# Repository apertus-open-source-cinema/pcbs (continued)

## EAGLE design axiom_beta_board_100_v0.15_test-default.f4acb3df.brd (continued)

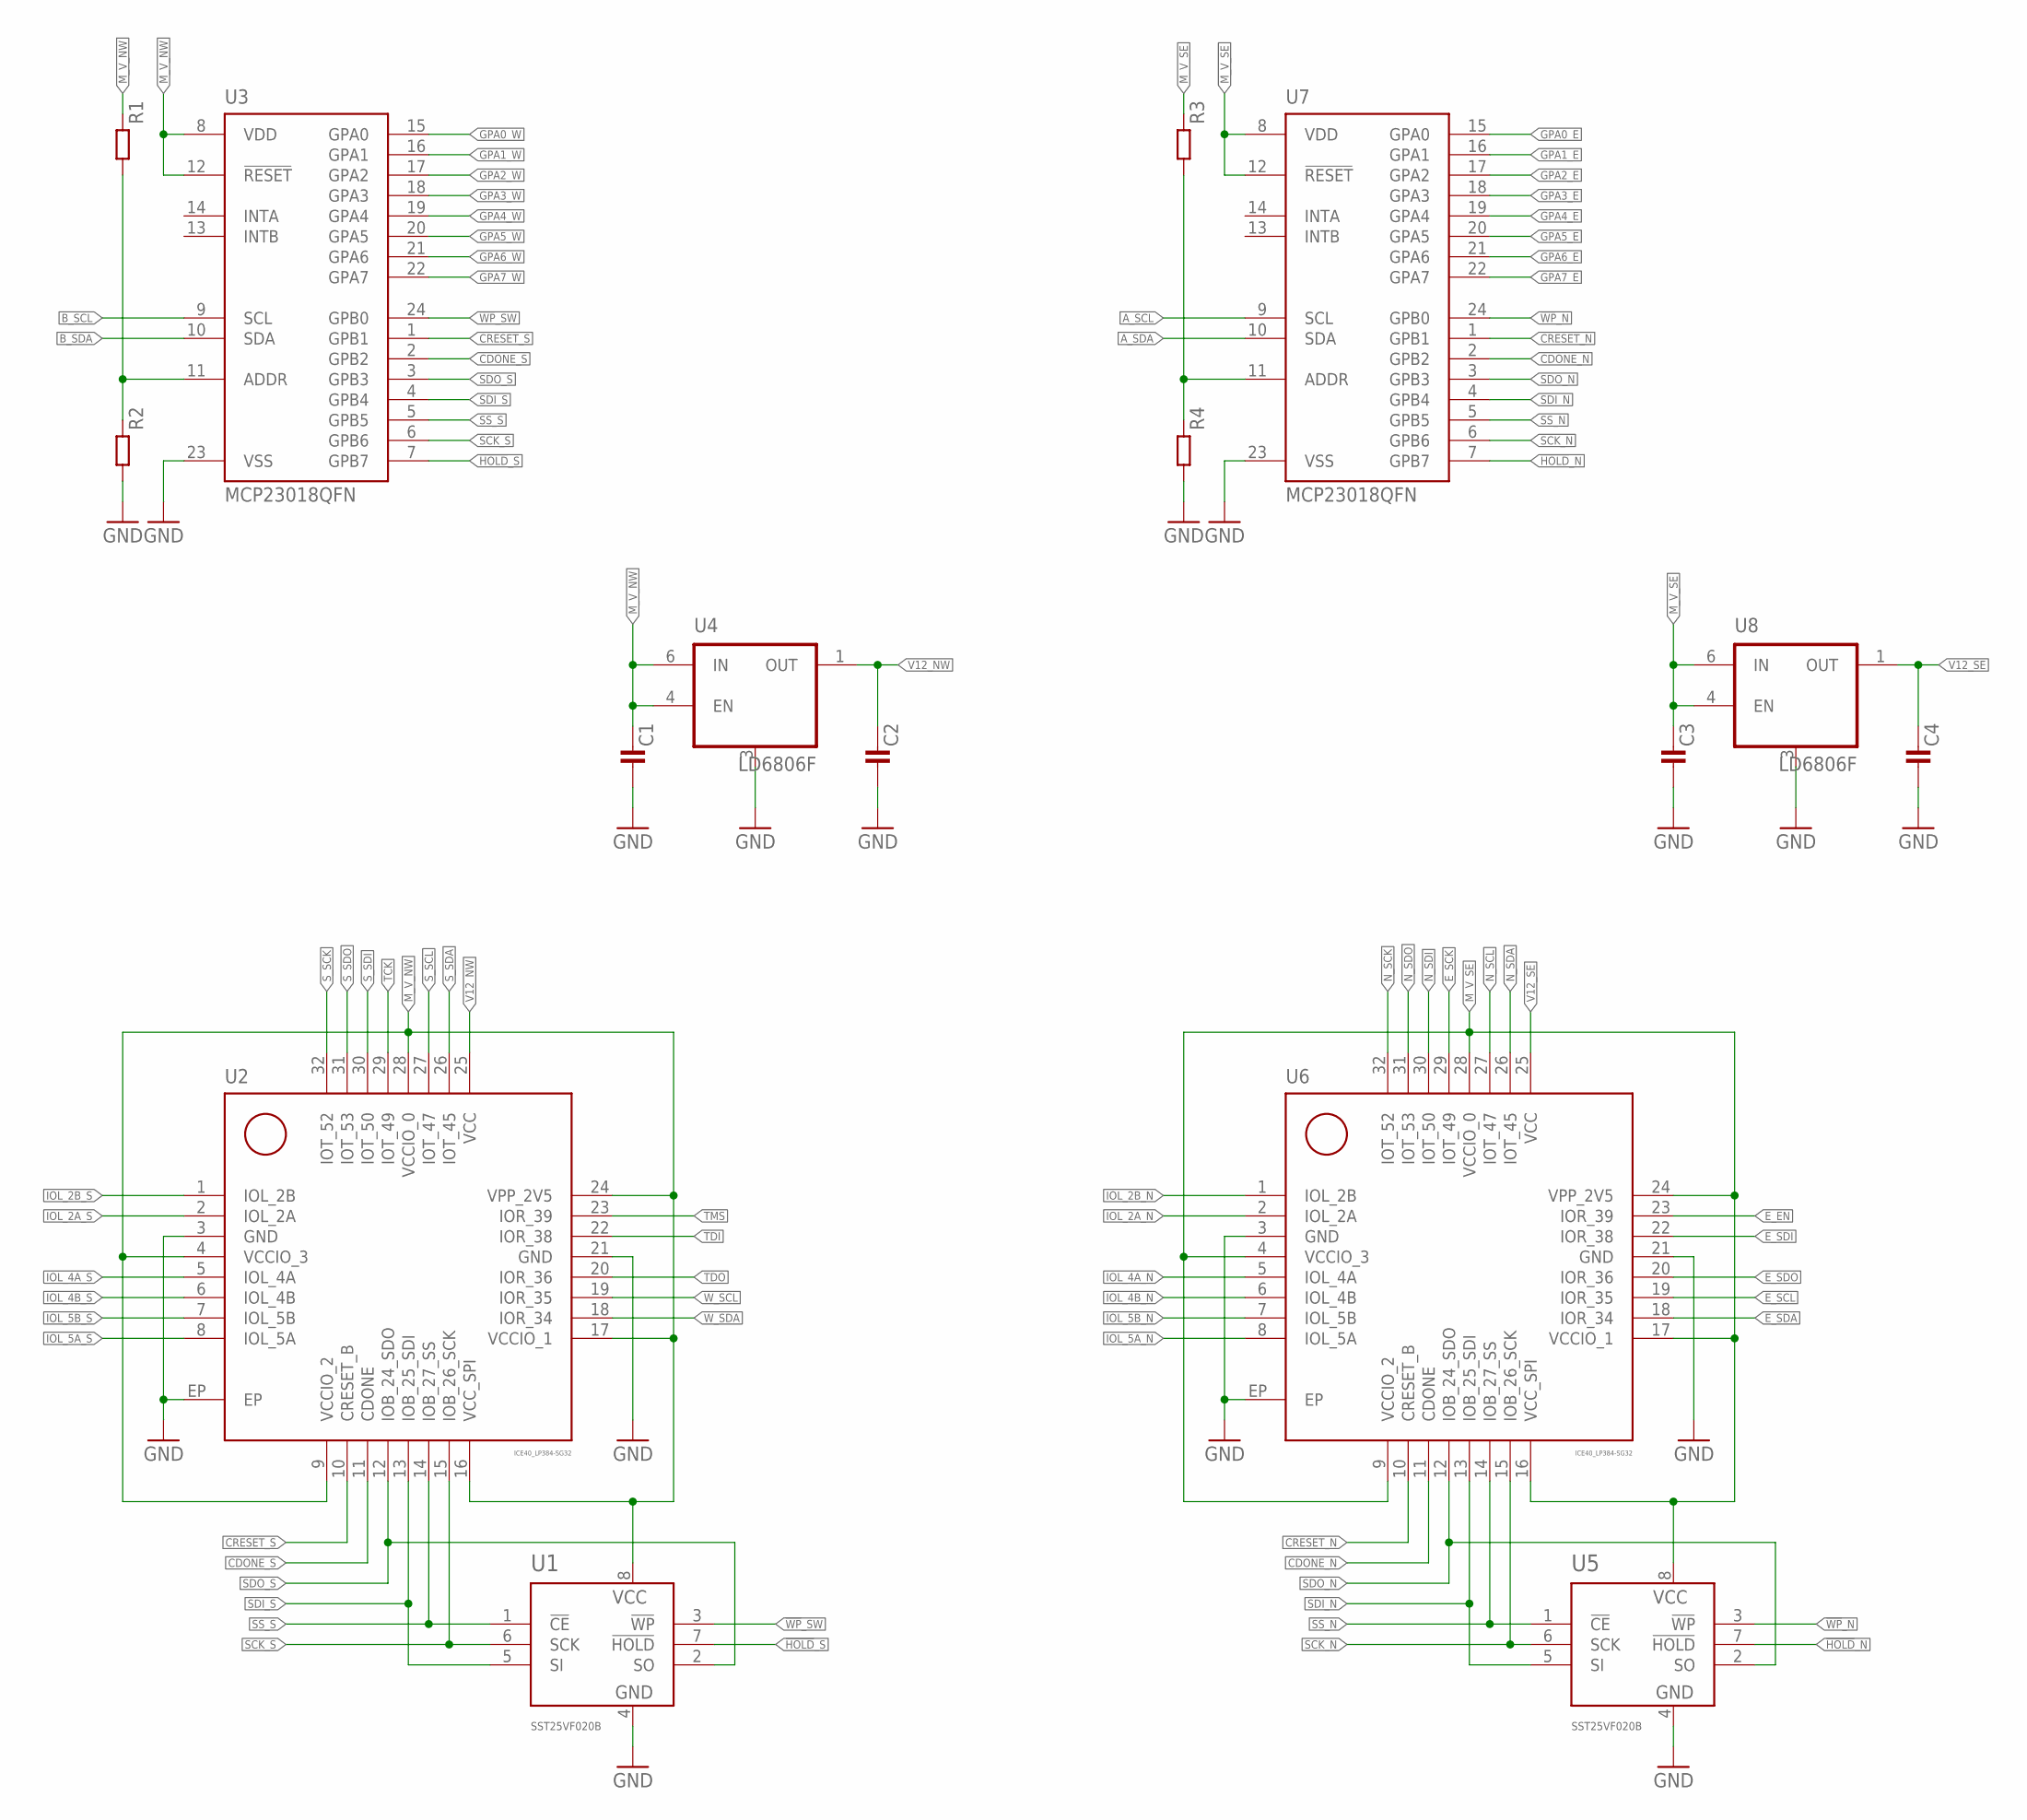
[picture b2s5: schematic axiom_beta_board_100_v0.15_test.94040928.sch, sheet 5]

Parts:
C1, C2, C3, C4: C0402-B; 0402-B
R1, R2, R3, R4: R0402-B; 0402-B
U1, U5: SST25VF020B; SOIC127P600X175-8N
U2, U6: ICE40_LP384-SG32; QFN-32
U3, U7: MCP23018QFN; QFN50P400X400X80-25N
U4, U8: LD6806F; DFN100X150X50-6N

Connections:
!HOLD!_N: U5.7 (!HOLD), U7.7 (GPB7)
!HOLD!_S: U1.7 (!HOLD), U3.7 (GPB7)
!WP!_N: U5.3 (!WP), U7.24 (GPB0)
!WP!_SW: U1.3 (!WP), U3.24 (GPB0)
CDONE_N: U6.11 (CDONE), U7.2 (GPB2)
CDONE_S: U2.11 (CDONE), U3.2 (GPB2)
CRESET_N: U6.10 (CRESET_B), U7.1 (GPB1)
CRESET_S: U2.10 (CRESET_B), U3.1 (GPB1)
E_EN: U6.23 (IOR_39); also elsewhere on the board
E_SCK: U6.29 (IOT_49); also elsewhere on the board
E_SCL: U6.19 (IOR_35); also elsewhere on the board
E_SDA: U6.18 (IOR_34); also elsewhere on the board
E_SDI: U6.22 (IOR_38); also elsewhere on the board
E_SDO: U6.20 (IOR_36); also elsewhere on the board
GND: C1.2, C2.2, C3.2, C4.2, R2.2, R4.2, U1.4 (VSS), U2.3 (GND), U2.21 (GND), U2.EP, U3.23 (VSS), U4.3 (GND), U5.4 (VSS), U6.3 (GND), U6.21 (GND), U6.EP, U7.23 (VSS), U8.3 (GND); also elsewhere on the board
GPA0_E: U7.15 (GPA0); also elsewhere on the board
GPA0_W: U3.15 (GPA0); also elsewhere on the board
GPA1_E: U7.16 (GPA1); also elsewhere on the board
GPA1_W: U3.16 (GPA1); also elsewhere on the board
GPA2_E: U7.17 (GPA2); also elsewhere on the board
GPA2_W: U3.17 (GPA2); also elsewhere on the board
GPA3_E: U7.18 (GPA3); also elsewhere on the board
GPA3_W: U3.18 (GPA3); also elsewhere on the board
GPA4_E: U7.19 (GPA4); also elsewhere on the board
GPA4_W: U3.19 (GPA4); also elsewhere on the board
GPA5_E: U7.20 (GPA5); also elsewhere on the board
GPA5_W: U3.20 (GPA5); also elsewhere on the board
GPA6_E: U7.21 (GPA6)
GPA6_W: U3.21 (GPA6)
GPA7_E: U7.22 (GPA7)
GPA7_W: U3.22 (GPA7)
IOL_2A_N: U6.2 (IOL_2A); also elsewhere on the board
IOL_2A_S: U2.2 (IOL_2A); also elsewhere on the board
IOL_2B_N: U6.1 (IOL_2B); also elsewhere on the board
IOL_2B_S: U2.1 (IOL_2B); also elsewhere on the board
IOL_4A_N: U6.5 (IOL_4A); also elsewhere on the board
IOL_4A_S: U2.5 (IOL_4A); also elsewhere on the board
IOL_4B_N: U6.6 (IOL_4B); also elsewhere on the board
IOL_4B_S: U2.6 (IOL_4B); also elsewhere on the board
IOL_5A_N: U6.8 (IOL_5A); also elsewhere on the board
IOL_5A_S: U2.8 (IOL_5A); also elsewhere on the board
IOL_5B_N: U6.7 (IOL_5B); also elsewhere on the board
IOL_5B_S: U2.7 (IOL_5B); also elsewhere on the board
M_V_NW: C1.1, R1.1, U1.8 (VCC), U2.4 (VCCIO_3), U2.9 (VCCIO_2), U2.16 (VCC_SPI), U2.17 (VCCIO_1), U2.24 (VPP_2V5), U2.28 (VCCIO_0), U3.8 (VDD), U3.12 (!RESET), U4.4 (EN), U4.6 (IN); also elsewhere on the board
M_V_SE: C3.1, R3.1, U5.8 (VCC), U6.4 (VCCIO_3), U6.9 (VCCIO_2), U6.16 (VCC_SPI), U6.17 (VCCIO_1), U6.24 (VPP_2V5), U6.28 (VCCIO_0), U7.8 (VDD), U7.12 (!RESET), U8.4 (EN), U8.6 (IN); also elsewhere on the board
unnamed: R3.2, R4.1, U7.11 (ADDR)
unnamed: R1.2, R2.1, U3.11 (ADDR)
N_SCK: U6.32 (IOT_52); also elsewhere on the board
N_SCL: U6.27 (IOT_47); also elsewhere on the board
N_SDA: U6.26 (IOT_45); also elsewhere on the board
N_SDI: U6.30 (IOT_50); also elsewhere on the board
N_SDO: U6.31 (IOT_53); also elsewhere on the board
SCK_N: U5.6 (SCK), U6.15 (IOB_26_SCK), U7.6 (GPB6)
SCK_S: U1.6 (SCK), U2.15 (IOB_26_SCK), U3.6 (GPB6)
SDI_N: U5.5 (SI), U6.13 (IOB_25_SDI), U7.4 (GPB4)
SDI_S: U1.5 (SI), U2.13 (IOB_25_SDI), U3.4 (GPB4)
SDO_N: U5.2 (SO), U6.12 (IOB_24_SDO), U7.3 (GPB3)
SDO_S: U1.2 (SO), U2.12 (IOB_24_SDO), U3.3 (GPB3)
SS_N: U5.1 (!CE), U6.14 (IOB_27_SS), U7.5 (GPB5)
SS_S: U1.1 (!CE), U2.14 (IOB_27_SS), U3.5 (GPB5)
S_SCK: U2.32 (IOT_52); also elsewhere on the board
S_SCL: U2.27 (IOT_47); also elsewhere on the board
S_SDA: U2.26 (IOT_45); also elsewhere on the board
S_SDI: U2.30 (IOT_50); also elsewhere on the board
S_SDO: U2.31 (IOT_53); also elsewhere on the board
TCK: U2.29 (IOT_49); also elsewhere on the board
TDI: U2.22 (IOR_38); also elsewhere on the board
TDO: U2.20 (IOR_36); also elsewhere on the board
TMS: U2.23 (IOR_39); also elsewhere on the board
V12_NW: C2.1, U2.25 (VCC), U4.1 (OUT)
V12_SE: C4.1, U6.25 (VCC), U8.1 (OUT)
W_SCL: U2.19 (IOR_35); also elsewhere on the board
W_SDA: U2.18 (IOR_34); also elsewhere on the board

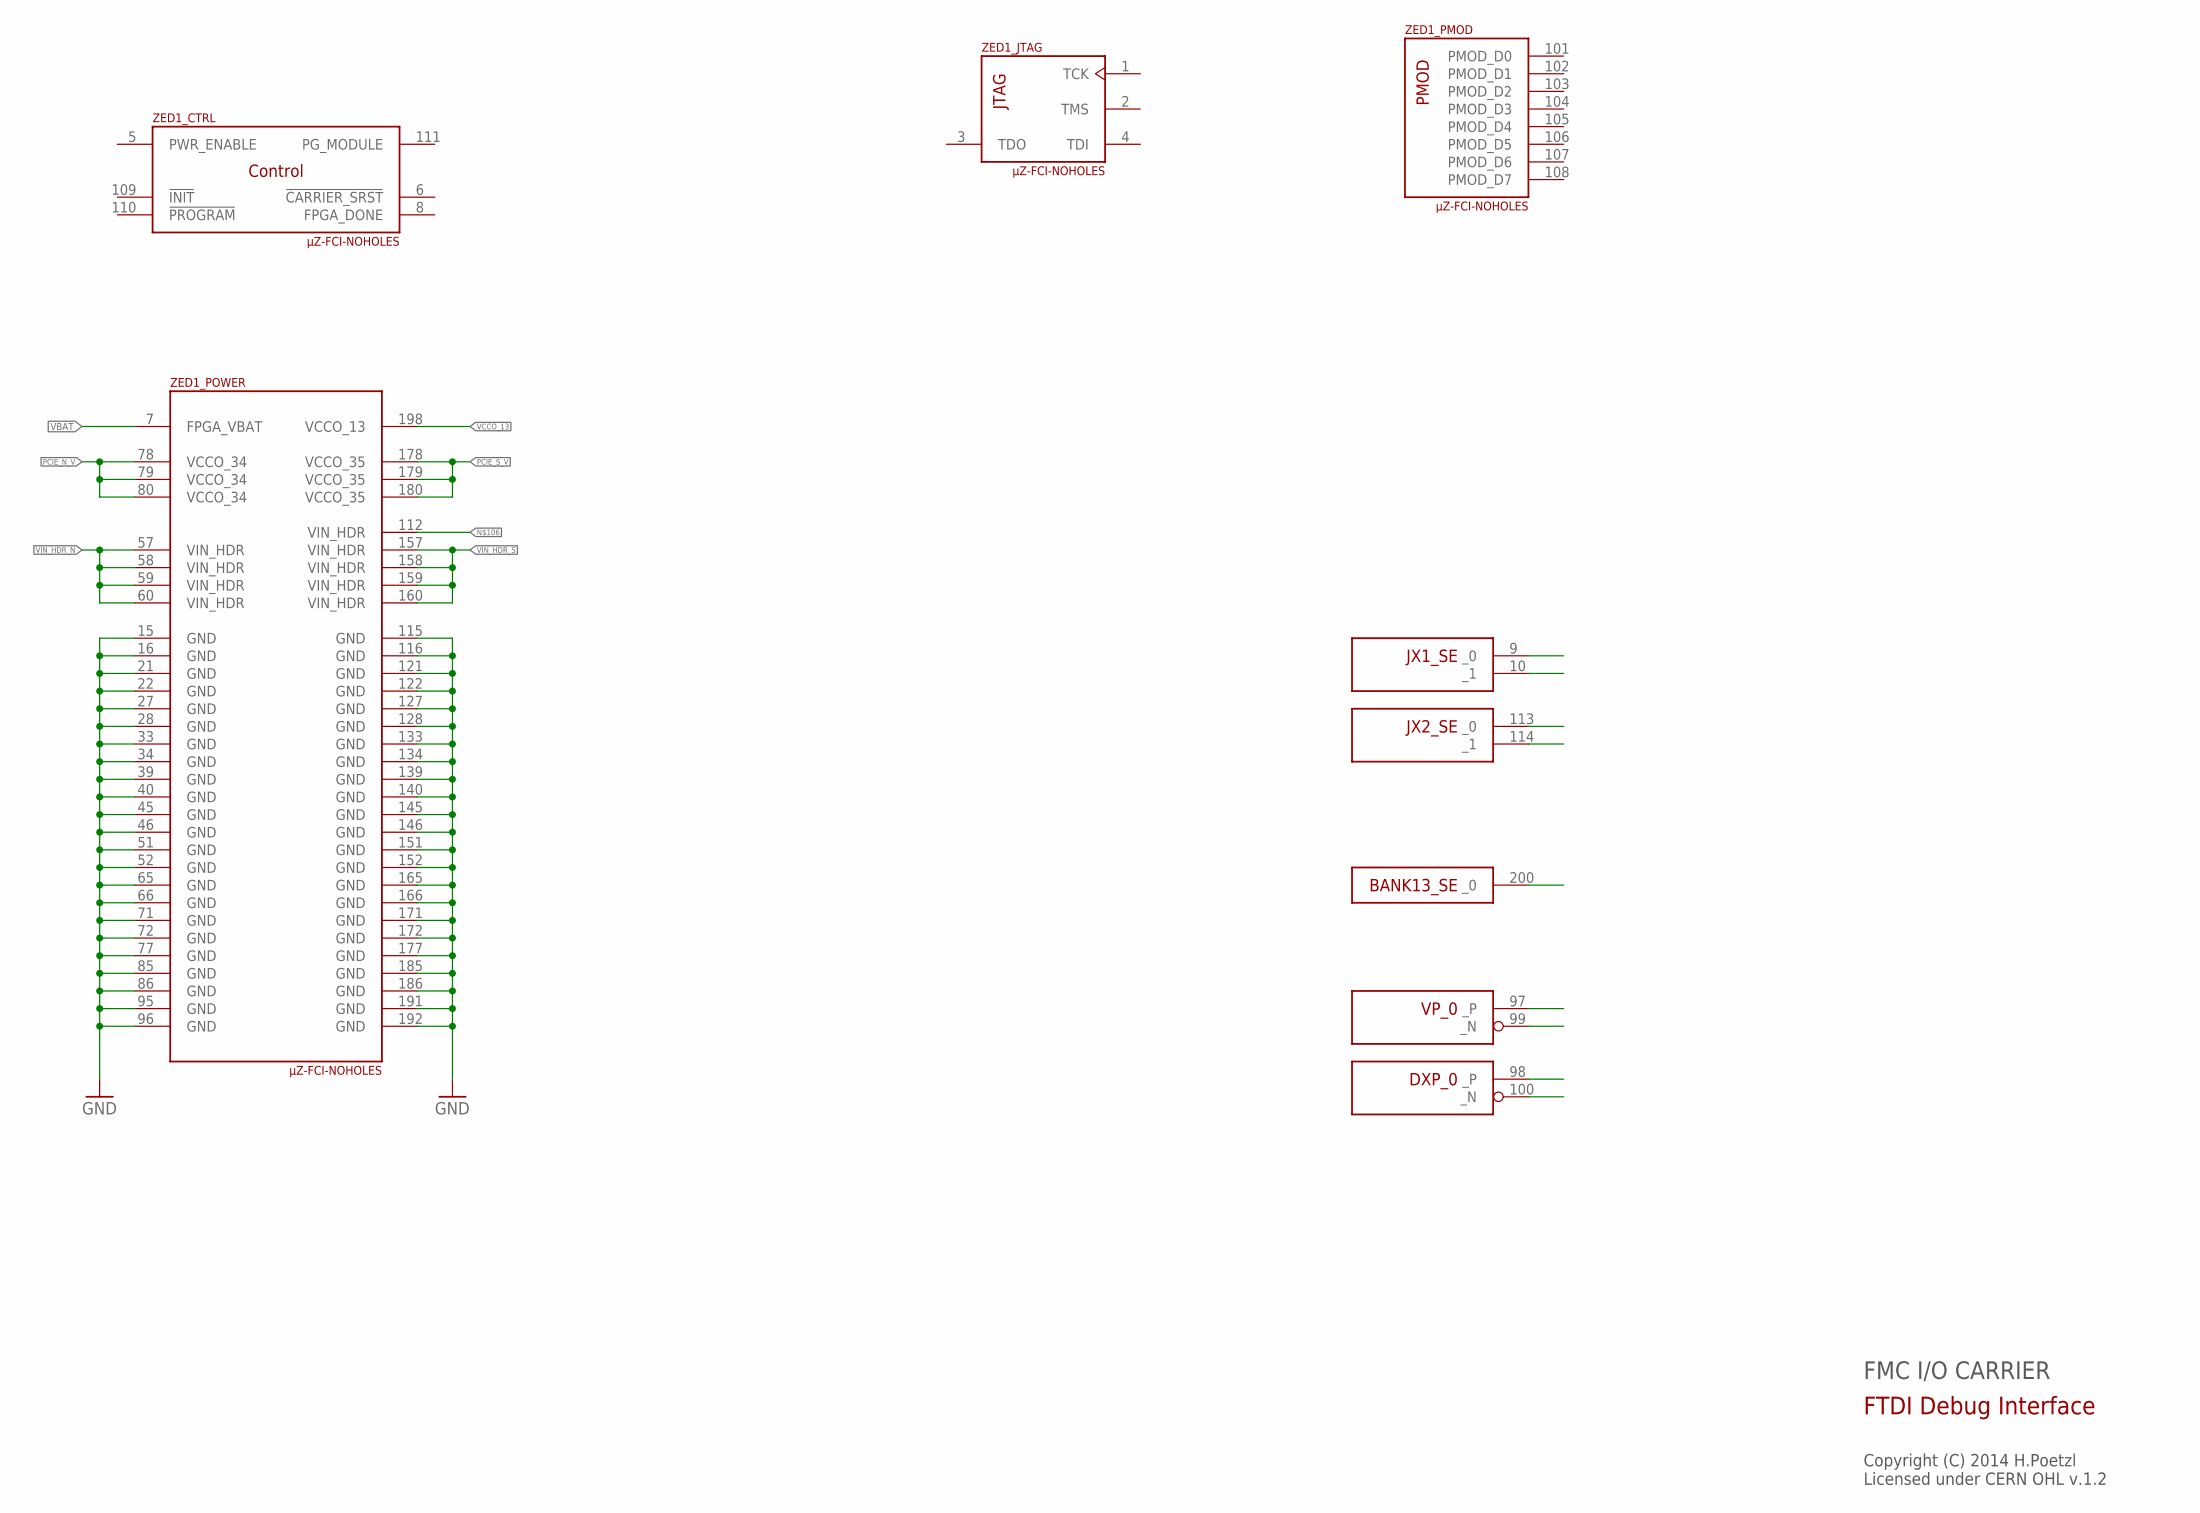
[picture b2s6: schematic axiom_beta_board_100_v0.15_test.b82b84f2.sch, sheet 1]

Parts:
ZED1: µZ-FCI-NOHOLES; µZ-NOHOLES

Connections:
GND: ZED1.15 (GND), ZED1.16 (GND), ZED1.21 (GND), ZED1.22 (GND), ZED1.27 (GND), ZED1.28 (GND), ZED1.33 (GND), ZED1.34 (GND), ZED1.39 (GND), ZED1.40 (GND), ZED1.45 (GND), ZED1.46 (GND), ZED1.51 (GND), ZED1.52 (GND), ZED1.65 (GND), ZED1.66 (GND), ZED1.71 (GND), ZED1.72 (GND), ZED1.77 (GND), ZED1.85 (GND), ZED1.86 (GND), ZED1.95 (GND), ZED1.96 (GND), ZED1.115 (GND), ZED1.116 (GND), ZED1.121 (GND), ZED1.122 (GND), ZED1.127 (GND), ZED1.128 (GND), ZED1.133 (GND), ZED1.134 (GND), ZED1.139 (GND), ZED1.140 (GND), ZED1.145 (GND), ZED1.146 (GND), ZED1.151 (GND), ZED1.152 (GND), ZED1.165 (GND), ZED1.166 (GND), ZED1.171 (GND), ZED1.172 (GND), ZED1.177 (GND), ZED1.185 (GND), ZED1.186 (GND), ZED1.191 (GND), ZED1.192 (GND); also elsewhere on the board
unnamed 266: ZED1.112 (VIN_HDR); also elsewhere on the board
PCIE_N_V: ZED1.78 (VCCO_34), ZED1.79 (VCCO_34), ZED1.80 (VCCO_34); also elsewhere on the board
PCIE_S_V: ZED1.178 (VCCO_35), ZED1.179 (VCCO_35), ZED1.180 (VCCO_35); also elsewhere on the board
VBAT: ZED1.7 (FPGA_VBAT); also elsewhere on the board
VCCO_13: ZED1.198 (VCCO_13)
VIN_HDR_N: ZED1.57 (VIN_HDR), ZED1.58 (VIN_HDR), ZED1.59 (VIN_HDR), ZED1.60 (VIN_HDR); also elsewhere on the board
VIN_HDR_S: ZED1.157 (VIN_HDR), ZED1.158 (VIN_HDR), ZED1.159 (VIN_HDR), ZED1.160 (VIN_HDR); also elsewhere on the board

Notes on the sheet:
FMC I/O CARRIER
Copyright (C) 2014 H.Poetzl Licensed under CERN OHL v.1.2
FTDI Debug Interface

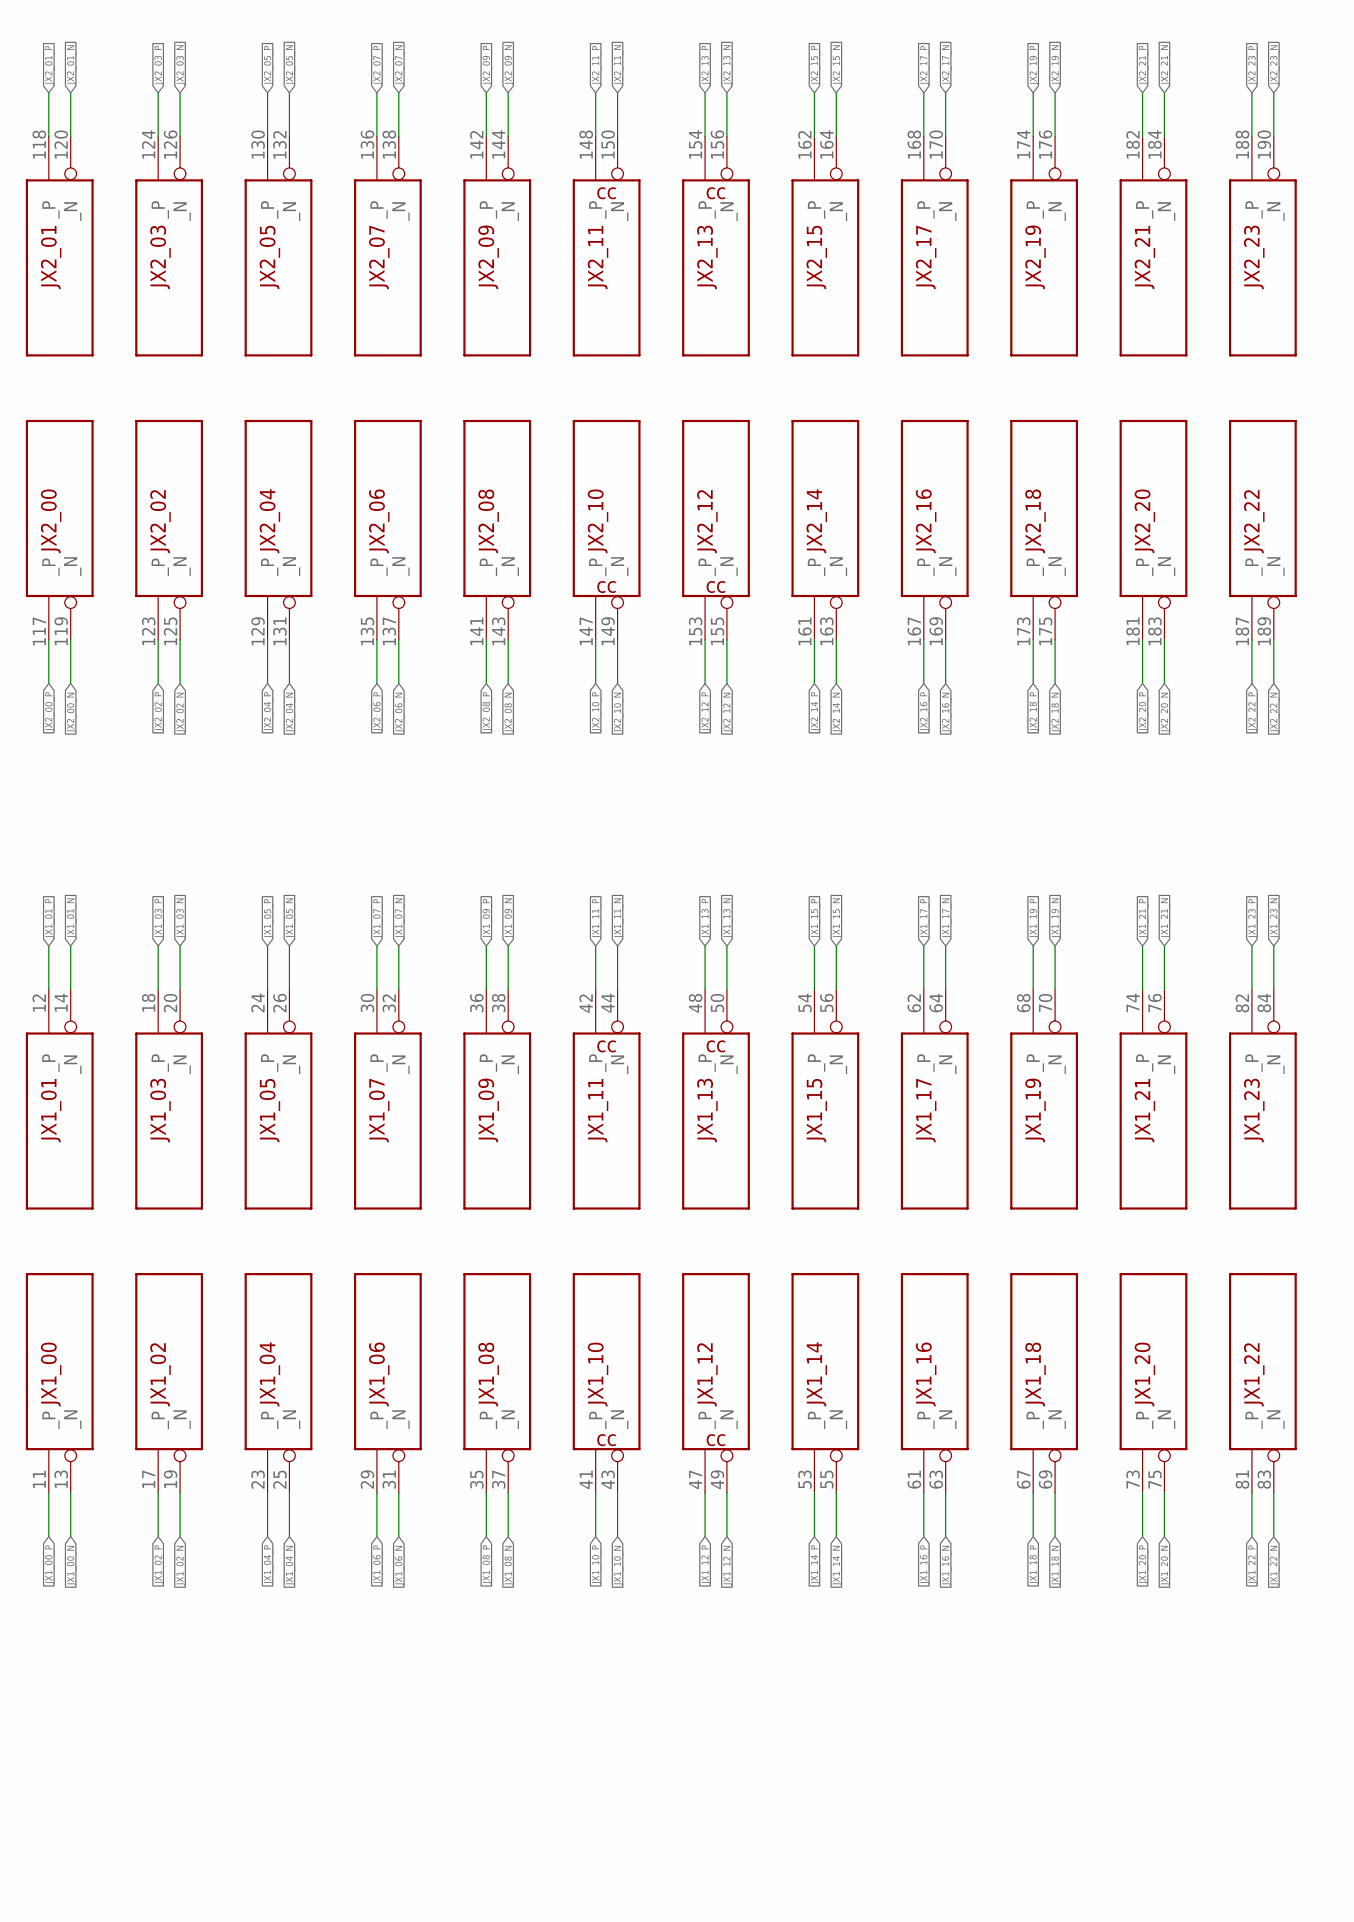
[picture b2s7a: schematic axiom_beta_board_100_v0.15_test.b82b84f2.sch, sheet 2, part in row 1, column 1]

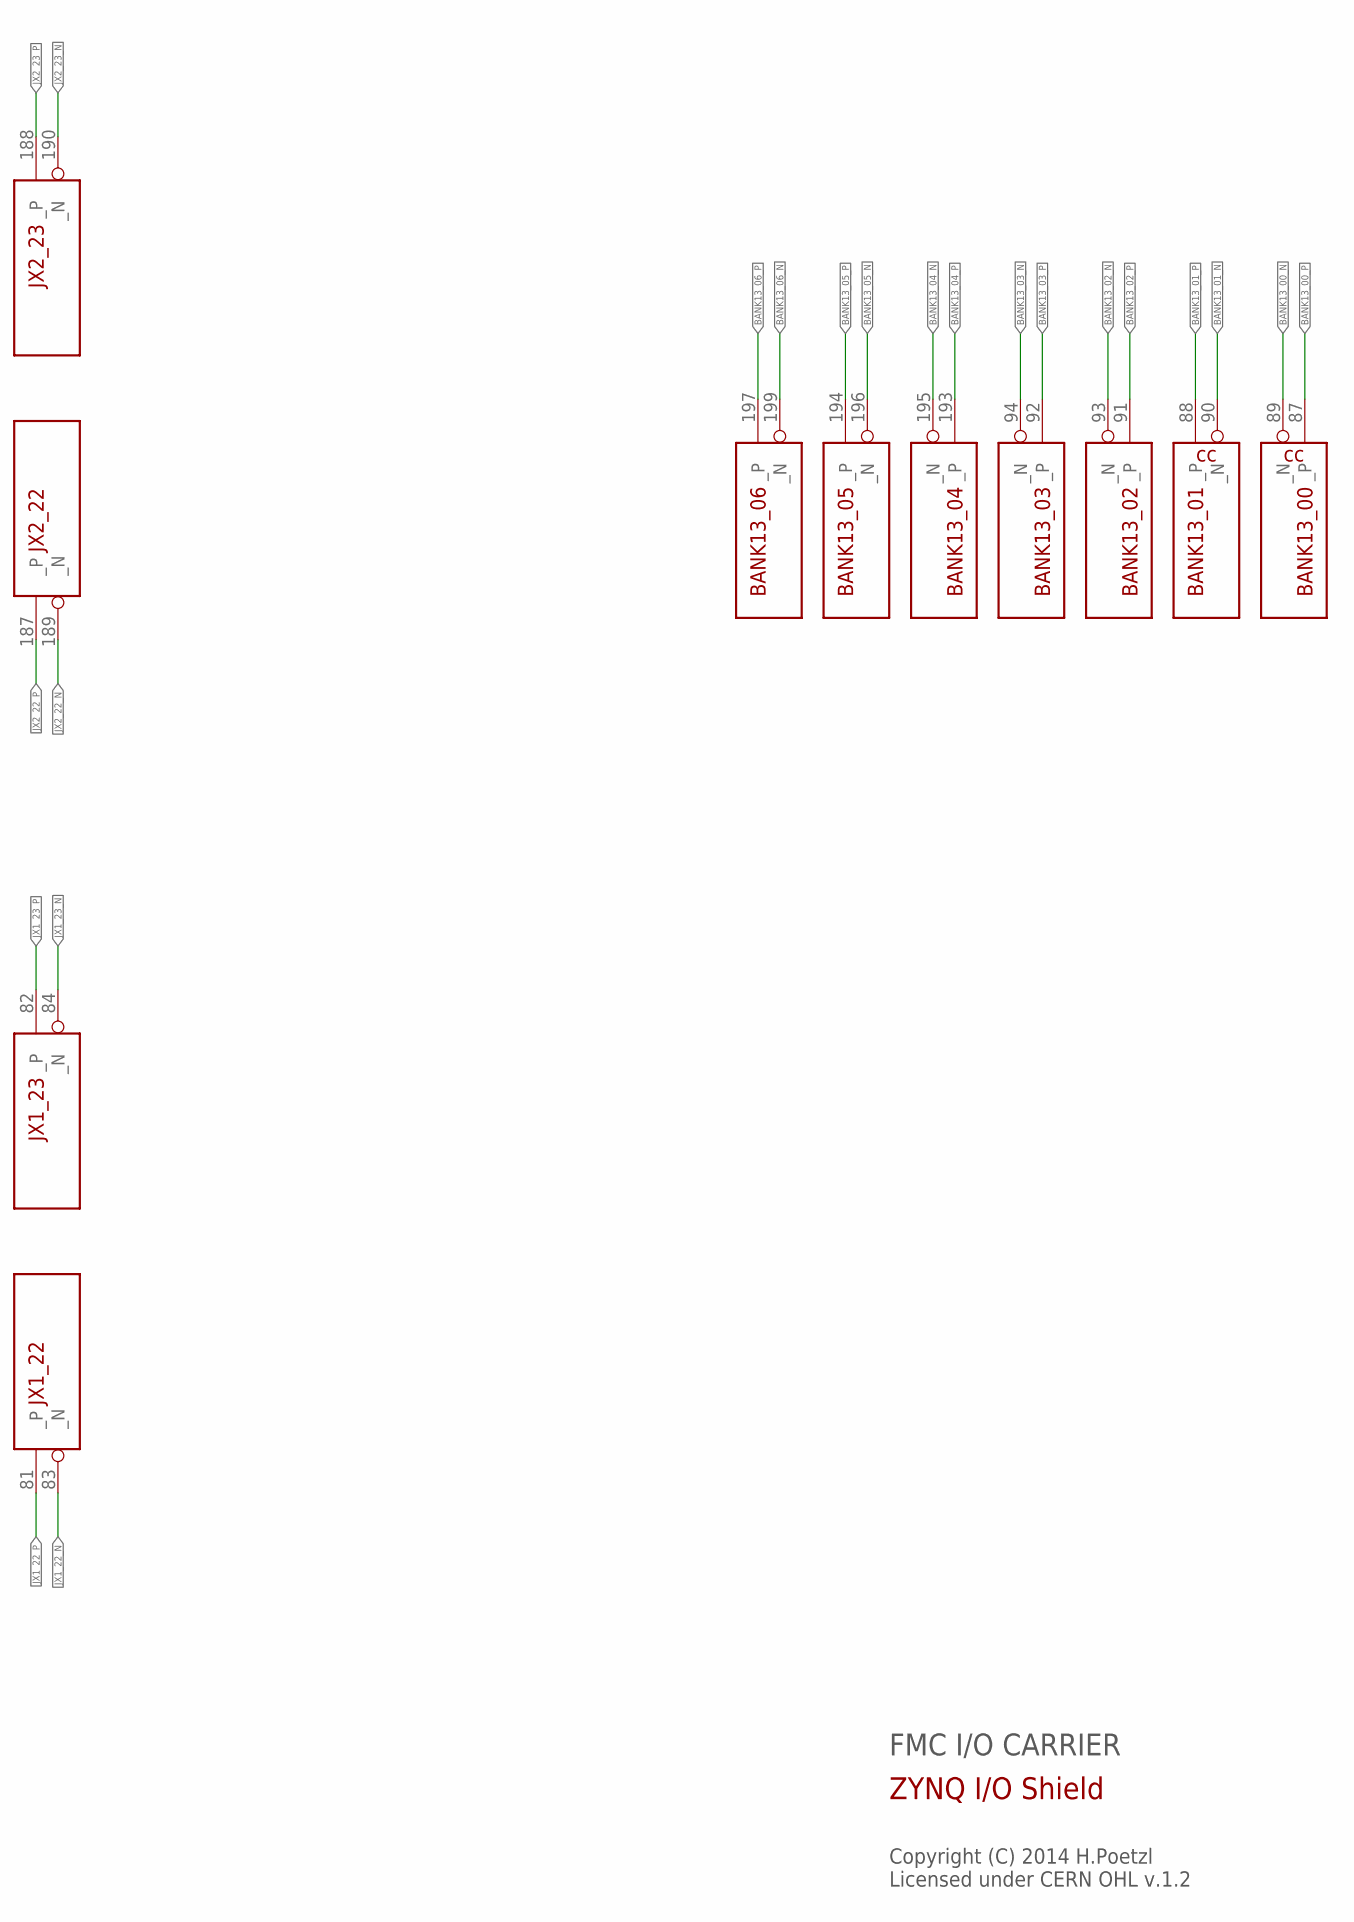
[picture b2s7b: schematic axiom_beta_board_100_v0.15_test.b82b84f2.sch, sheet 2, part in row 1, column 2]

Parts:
ZED1: µZ-FCI-NOHOLES; µZ-NOHOLES

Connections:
BANK13_00_N: ZED1.89 (_N); also elsewhere on the board
BANK13_00_P: ZED1.87 (_P); also elsewhere on the board
BANK13_01_N: ZED1.90 (_N); also elsewhere on the board
BANK13_01_P: ZED1.88 (_P); also elsewhere on the board
BANK13_02_N: ZED1.93 (_N); also elsewhere on the board
BANK13_02_P: ZED1.91 (_P); also elsewhere on the board
BANK13_03_N: ZED1.94 (_N); also elsewhere on the board
BANK13_03_P: ZED1.92 (_P); also elsewhere on the board
BANK13_04_N: ZED1.195 (_N); also elsewhere on the board
BANK13_04_P: ZED1.193 (_P); also elsewhere on the board
BANK13_05_N: ZED1.196 (_N); also elsewhere on the board
BANK13_05_P: ZED1.194 (_P); also elsewhere on the board
BANK13_06_N: ZED1.199 (_N); also elsewhere on the board
BANK13_06_P: ZED1.197 (_P); also elsewhere on the board
JX1_00_N: ZED1.13 (_N); also elsewhere on the board
JX1_00_P: ZED1.11 (_P); also elsewhere on the board
JX1_01_N: ZED1.14 (_N); also elsewhere on the board
JX1_01_P: ZED1.12 (_P); also elsewhere on the board
JX1_02_N: ZED1.19 (_N); also elsewhere on the board
JX1_02_P: ZED1.17 (_P); also elsewhere on the board
JX1_03_N: ZED1.20 (_N); also elsewhere on the board
JX1_03_P: ZED1.18 (_P); also elsewhere on the board
JX1_04_N: ZED1.25 (_N); also elsewhere on the board
JX1_04_P: ZED1.23 (_P); also elsewhere on the board
JX1_05_N: ZED1.26 (_N); also elsewhere on the board
JX1_05_P: ZED1.24 (_P); also elsewhere on the board
JX1_06_N: ZED1.31 (_N); also elsewhere on the board
JX1_06_P: ZED1.29 (_P); also elsewhere on the board
JX1_07_N: ZED1.32 (_N); also elsewhere on the board
JX1_07_P: ZED1.30 (_P); also elsewhere on the board
JX1_08_N: ZED1.37 (_N); also elsewhere on the board
JX1_08_P: ZED1.35 (_P); also elsewhere on the board
JX1_09_N: ZED1.38 (_N); also elsewhere on the board
JX1_09_P: ZED1.36 (_P); also elsewhere on the board
JX1_10_N: ZED1.43 (_N); also elsewhere on the board
JX1_10_P: ZED1.41 (_P); also elsewhere on the board
JX1_11_N: ZED1.44 (_N); also elsewhere on the board
JX1_11_P: ZED1.42 (_P); also elsewhere on the board
JX1_12_N: ZED1.49 (_N); also elsewhere on the board
JX1_12_P: ZED1.47 (_P); also elsewhere on the board
JX1_13_N: ZED1.50 (_N); also elsewhere on the board
JX1_13_P: ZED1.48 (_P); also elsewhere on the board
JX1_14_N: ZED1.55 (_N); also elsewhere on the board
JX1_14_P: ZED1.53 (_P); also elsewhere on the board
JX1_15_N: ZED1.56 (_N); also elsewhere on the board
JX1_15_P: ZED1.54 (_P); also elsewhere on the board
JX1_16_N: ZED1.63 (_N); also elsewhere on the board
JX1_16_P: ZED1.61 (_P); also elsewhere on the board
JX1_17_N: ZED1.64 (_N); also elsewhere on the board
JX1_17_P: ZED1.62 (_P); also elsewhere on the board
JX1_18_N: ZED1.69 (_N); also elsewhere on the board
JX1_18_P: ZED1.67 (_P); also elsewhere on the board
JX1_19_N: ZED1.70 (_N); also elsewhere on the board
JX1_19_P: ZED1.68 (_P); also elsewhere on the board
JX1_20_N: ZED1.75 (_N); also elsewhere on the board
JX1_20_P: ZED1.73 (_P); also elsewhere on the board
JX1_21_N: ZED1.76 (_N); also elsewhere on the board
JX1_21_P: ZED1.74 (_P); also elsewhere on the board
JX1_22_N: ZED1.83 (_N); also elsewhere on the board
JX1_22_P: ZED1.81 (_P); also elsewhere on the board
JX1_23_N: ZED1.84 (_N); also elsewhere on the board
JX1_23_P: ZED1.82 (_P); also elsewhere on the board
JX2_00_N: ZED1.119 (_N); also elsewhere on the board
JX2_00_P: ZED1.117 (_P); also elsewhere on the board
JX2_01_N: ZED1.120 (_N); also elsewhere on the board
JX2_01_P: ZED1.118 (_P); also elsewhere on the board
JX2_02_N: ZED1.125 (_N); also elsewhere on the board
JX2_02_P: ZED1.123 (_P); also elsewhere on the board
JX2_03_N: ZED1.126 (_N); also elsewhere on the board
JX2_03_P: ZED1.124 (_P); also elsewhere on the board
JX2_04_N: ZED1.131 (_N); also elsewhere on the board
JX2_04_P: ZED1.129 (_P); also elsewhere on the board
JX2_05_N: ZED1.132 (_N); also elsewhere on the board
JX2_05_P: ZED1.130 (_P); also elsewhere on the board
JX2_06_N: ZED1.137 (_N); also elsewhere on the board
JX2_06_P: ZED1.135 (_P); also elsewhere on the board
JX2_07_N: ZED1.138 (_N); also elsewhere on the board
JX2_07_P: ZED1.136 (_P); also elsewhere on the board
JX2_08_N: ZED1.143 (_N); also elsewhere on the board
JX2_08_P: ZED1.141 (_P); also elsewhere on the board
JX2_09_N: ZED1.144 (_N); also elsewhere on the board
JX2_09_P: ZED1.142 (_P); also elsewhere on the board
JX2_10_N: ZED1.149 (_N); also elsewhere on the board
JX2_10_P: ZED1.147 (_P); also elsewhere on the board
JX2_11_N: ZED1.150 (_N); also elsewhere on the board
JX2_11_P: ZED1.148 (_P); also elsewhere on the board
JX2_12_N: ZED1.155 (_N); also elsewhere on the board
JX2_12_P: ZED1.153 (_P); also elsewhere on the board
JX2_13_N: ZED1.156 (_N); also elsewhere on the board
JX2_13_P: ZED1.154 (_P); also elsewhere on the board
JX2_14_N: ZED1.163 (_N); also elsewhere on the board
JX2_14_P: ZED1.161 (_P); also elsewhere on the board
JX2_15_N: ZED1.164 (_N); also elsewhere on the board
JX2_15_P: ZED1.162 (_P); also elsewhere on the board
JX2_16_N: ZED1.169 (_N); also elsewhere on the board
JX2_16_P: ZED1.167 (_P); also elsewhere on the board
JX2_17_N: ZED1.170 (_N); also elsewhere on the board
JX2_17_P: ZED1.168 (_P); also elsewhere on the board
JX2_18_N: ZED1.175 (_N); also elsewhere on the board
JX2_18_P: ZED1.173 (_P); also elsewhere on the board
JX2_19_N: ZED1.176 (_N); also elsewhere on the board
JX2_19_P: ZED1.174 (_P); also elsewhere on the board
JX2_20_N: ZED1.183 (_N); also elsewhere on the board
JX2_20_P: ZED1.181 (_P); also elsewhere on the board
JX2_21_N: ZED1.184 (_N); also elsewhere on the board
JX2_21_P: ZED1.182 (_P); also elsewhere on the board
JX2_22_N: ZED1.189 (_N); also elsewhere on the board
JX2_22_P: ZED1.187 (_P); also elsewhere on the board
JX2_23_N: ZED1.190 (_N); also elsewhere on the board
JX2_23_P: ZED1.188 (_P); also elsewhere on the board

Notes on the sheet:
FMC I/O CARRIER
Copyright (C) 2014 H.Poetzl Licensed under CERN OHL v.1.2
ZYNQ I/O Shield
